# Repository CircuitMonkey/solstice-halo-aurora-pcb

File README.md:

# solstice-core-starfire-pcb
Solstice Design System —  *Aurora* HaLo —  Eagle PCB

PCB files for the **Circuit Monkey** *Aurora* **Solstice** *HaLo*

Format is EagleCAD 9.x schematic and board layout

*Aurora* is a *Solstice* Hardware Locus (HaLo) module/shield.  The Aurora allows you to add a prototyping perf-board to the top of your Solstice Core module.

For more details, check out the product page at

  * https://www.tindie.com/products/15591/

### Revision Notes
* Rev. 0 - Initial board design.  This revision was made for evaluation and only
one unit ever made.  Not shared in this repository.

* Rev. A - First revision meant for human consumption.

* Rev. B - Fixed Vin and GND pins swapped. First for-sale version.

#### Rev A. Issues:
  * Forgot to swap Vin and GND pins on HaLo connector.   Vin was dangerously close to GND mounting hole.  Was swapped on core StarFire board but we goofed in updating the Rev. A design for this board.  Solution for now is to pluck connector pins 1 and 2 out of HL4 passthrough connector prior to soldering.  Also, black sharpie the legend for those to pins.  Attempting to use these pins would short Vin to GND.

#### Rev B. Issues:
    * No known issues.

## Designed by Circuit Monkey in Las Vegas, Nevada, USA
MIT License.

All text above must be included in any redistribution

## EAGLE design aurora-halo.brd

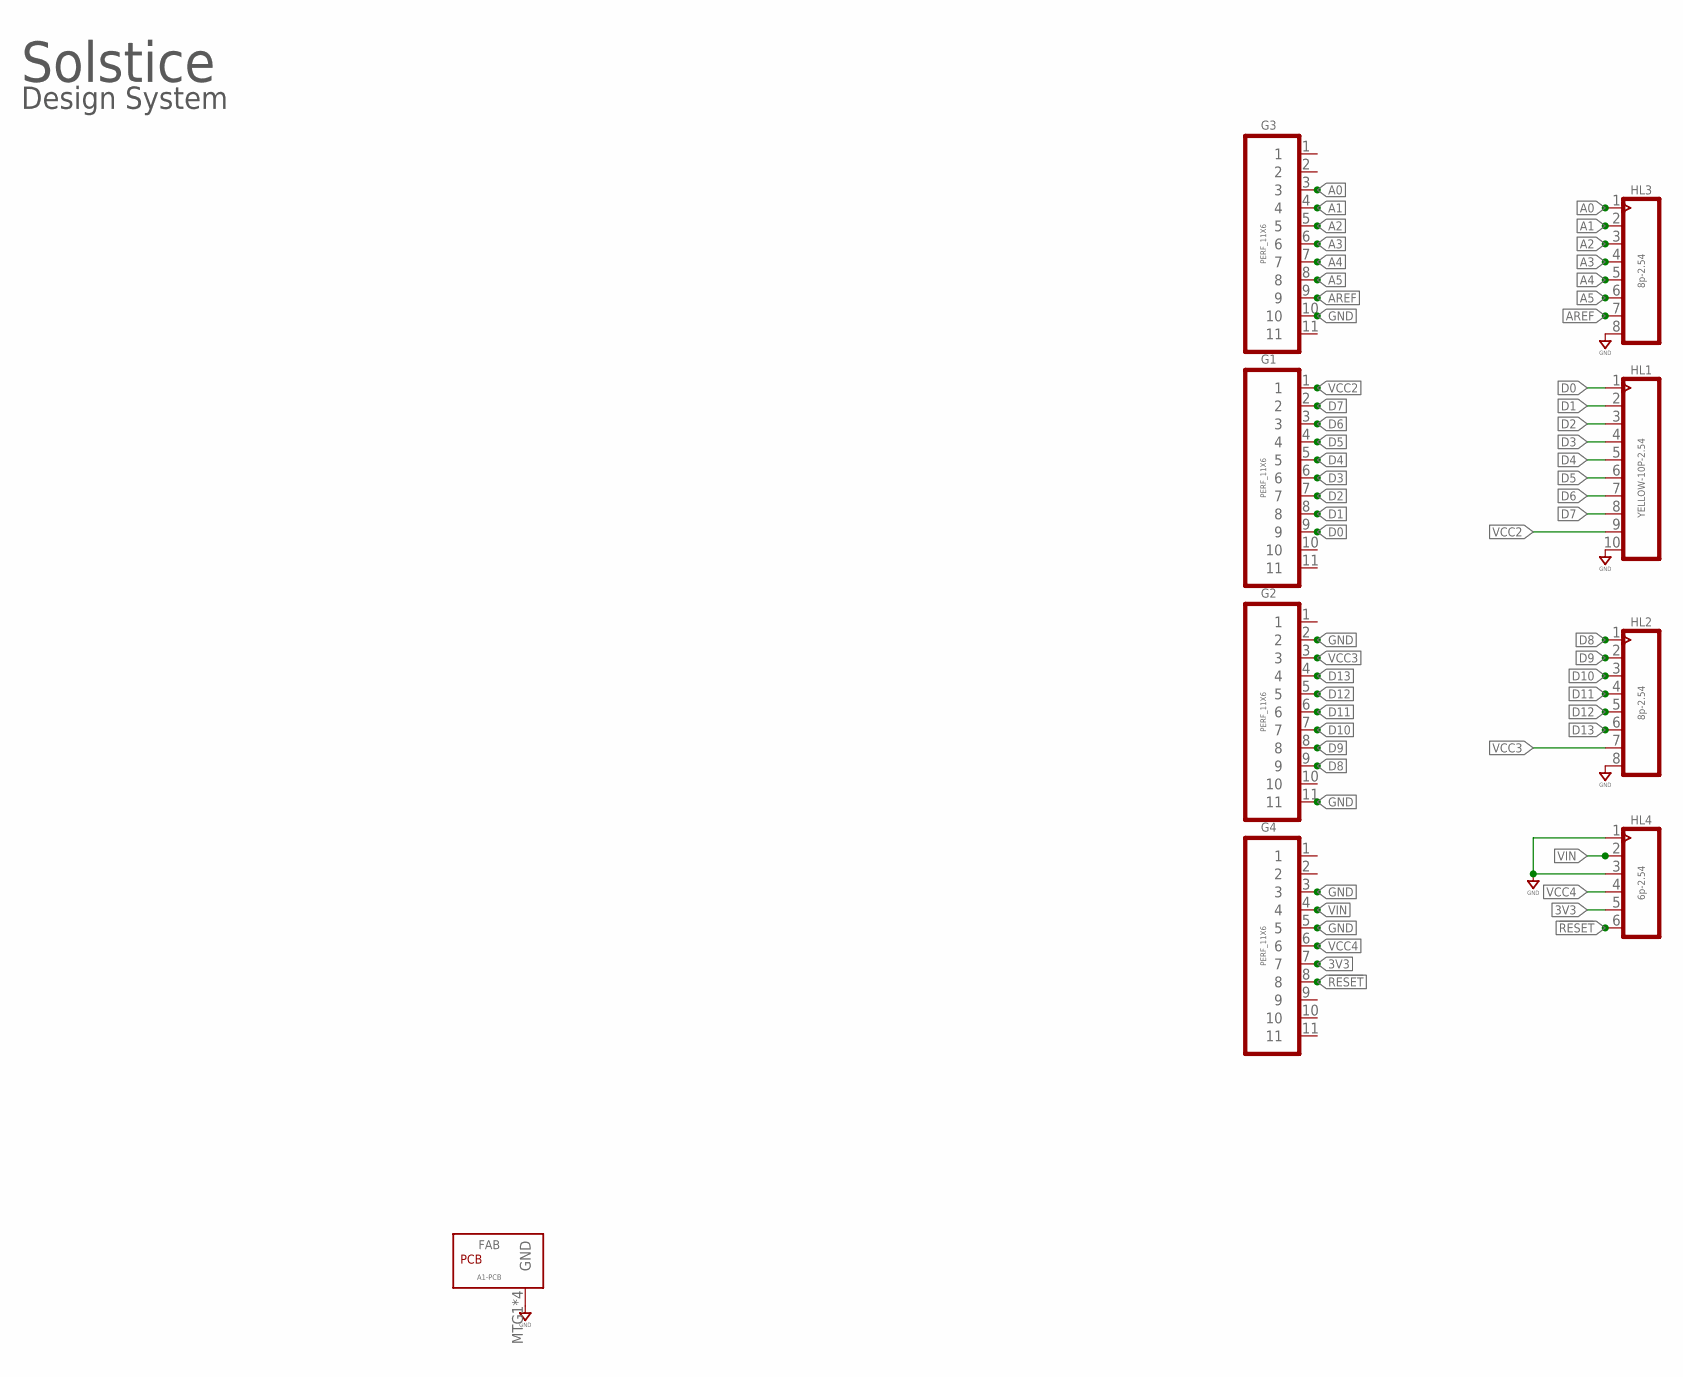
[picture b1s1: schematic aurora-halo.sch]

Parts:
FAB: A1-PCB; PCB-HALO-A1
G1, G2, G3, G4: PERF_11X6; PERF_6X11
HL1: YELLOW-10P-2.54; H10-2.54
HL2, HL3: 8p-2.54; H8-2.54
HL4: 6p-2.54; H6-2.54

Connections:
3V3: G4.7, HL4.5
!RESET: G4.8, HL4.6
A0: G3.3, HL3.1
A1: G3.4, HL3.2
A2: G3.5, HL3.3
A3: G3.6, HL3.4
A4: G3.7, HL3.5
A5: G3.8, HL3.6
AREF: G3.9, HL3.7
D0: G1.9, HL1.1
D1: G1.8, HL1.2
D2: G1.7, HL1.3
D3: G1.6, HL1.4
D4: G1.5, HL1.5
D5: G1.4, HL1.6
D6: G1.3, HL1.7
D7: G1.2, HL1.8
D8: G2.9, HL2.1
D9: G2.8, HL2.2
D10: G2.7, HL2.3
D11: G2.6, HL2.4
D12: G2.5, HL2.5
D13: G2.4, HL2.6
GND: FAB.MTG1, FAB.MTG2, FAB.MTG3, FAB.MTG4, G2.2, G2.11, G3.10, G4.3, G4.5, HL1.10, HL2.8, HL3.8, HL4.1, HL4.3
VCC2: G1.1, HL1.9
VCC3: G2.3, HL2.7
VCC4: G4.6, HL4.4
VIN: G4.4, HL4.2

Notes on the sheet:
Solstice
Design System

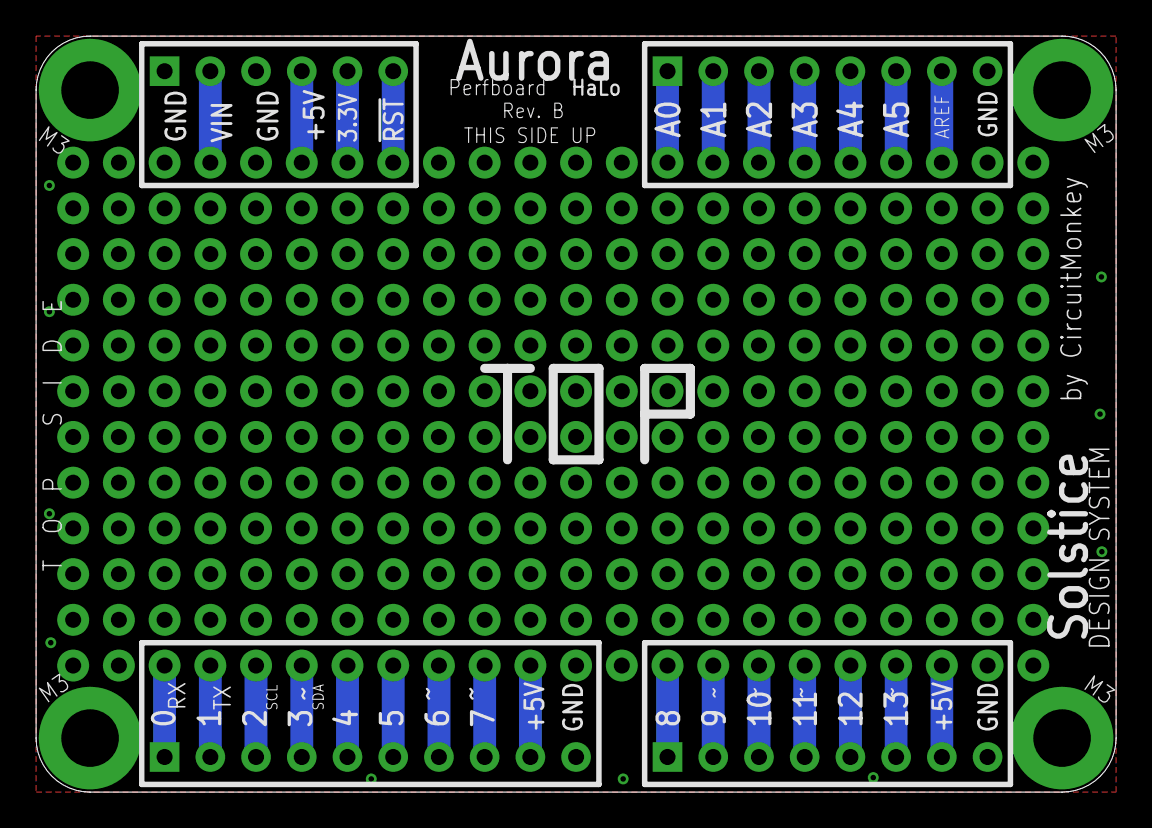
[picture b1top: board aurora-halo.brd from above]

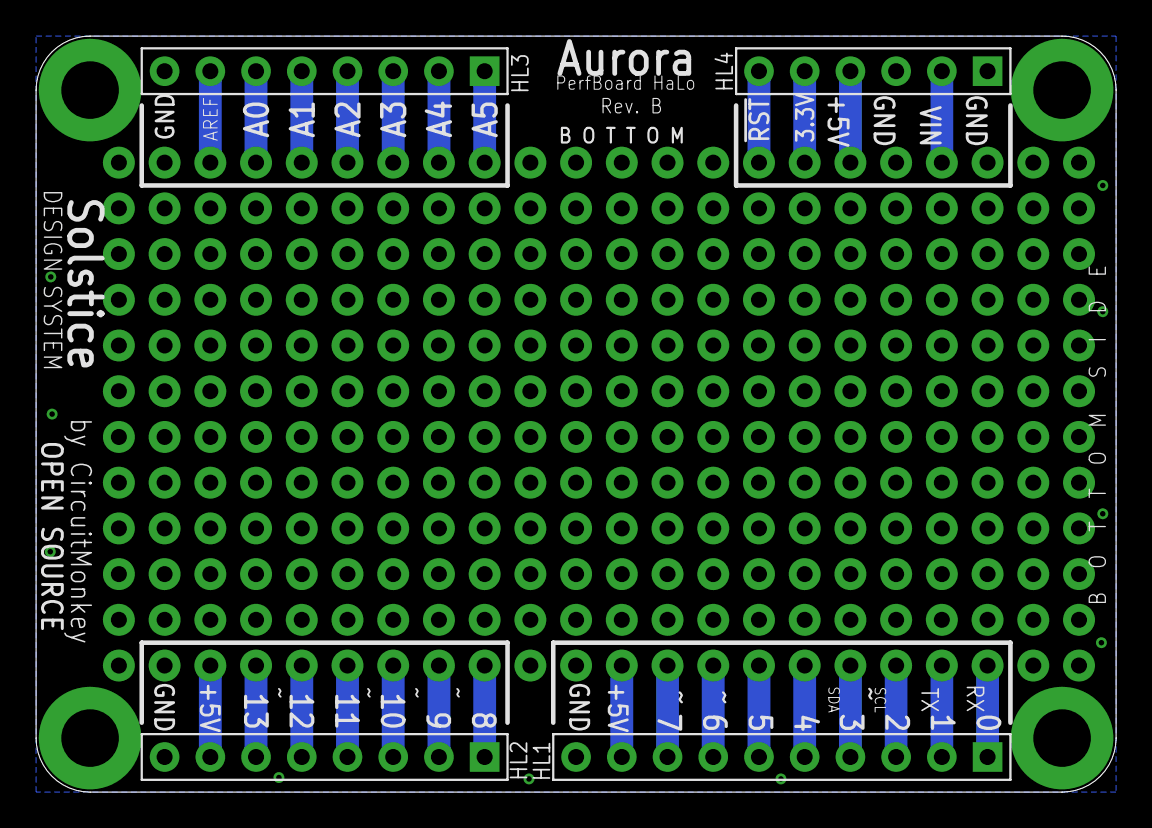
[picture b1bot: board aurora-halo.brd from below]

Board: 2 copper layers, 60.0 x 42.0 mm, 9 parts (4 on the bottom side), 28 nets.

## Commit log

2018-10-30 Publish Aurora HaLo Rev. A PCB.
2018-10-31 Update README.md
    License is MIT. Copy/paste goof from Solstice Core readme.md, which is Creative Commons because it was derived from Arduino. Our HaLo boards are not Arduino derivative in design.
2018-12-03 Update PCB to Rev. B
